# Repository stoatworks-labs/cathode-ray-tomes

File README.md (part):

# Cathode Ray Tomes

> **AI-assisted project.** This codebase was created with [Claude](https://claude.com/claude-code)
> (Anthropic), directed and reviewed by a human author.
> I've run the corpus index, the ingestion pipeline and the web application end to end against
> the real ArcadeRTFM corpus. The Pong KiCad conversion has a verified component complement and
> BOM, but only eight of its signal nets (the video output chain) have been traced. The Battlezone
> Math Box and Tempest auxiliary boards are traced in full, every net on their drawings, and each
> redrawn schematic is checked against its read by KiCad's own netlist. Nothing here has been
> checked against physical hardware.

Modern, searchable editions of service documentation: arcade boards, and the
consoles that came after them.

**It's here to help you fix boards.** The board conversions are
diagnostic aids. They answer "which chip is at C4, what does it do, and am I even
looking at the right revision", and they aren't trying to be complete clones.
A partial complement that gets you to the right chip is useful; a complete one
that's wrong about your board revision isn't. That's why Asteroids ships as
four separate boards rather than one averaged guess.

Arcade service manuals survive almost entirely as flat scans: page images with no text
layer, no structure and no way to search them. Cathode Ray Tomes rebuilds them as web
documents, with every page OCR'd and searchable, every machine cross-referenced against its
hardware specification and DIP switch settings, and (for a small number of boards) the
schematic rebuilt as a proper KiCad project with an accurate bill of materials.

Console service manuals are a different problem, and a much nicer one. Most of them
are native vector with a real text layer, so their schematic sheets already carry
designators, values and net names as text rather than as ink, which leaves nothing to OCR
and nothing to trace. Eleven consoles and handhelds are here, with 42 documents between
them; see `docs/EXTERNAL-SOURCES.md` for where they came from.

Not all of those are service manuals, and they don't pretend to be. Development
manuals and modchip installation guides have their own document types and sort after
every kind of service material, so a machine page shows the service manuals first.

## What the corpus actually is

I measured this rather than assuming it, from `https://arcadertfm.com/machines.json` and the
PDFs themselves:

| | |
|---|---|
| Machines (MAME-derived metadata) | 7,812 |
| Machines with documents | 1,384 |
| PDFs | 2,405 (~4.7 GB) |
| Schematic / drawing / wiring documents | 506 |
| PDFs containing a text layer | **0** |
| PDFs containing vector artwork | **0** |

Every page of every document is a single embedded raster image: bilevel CCITT/JBIG2 at
200–300 dpi for line drawings, JPEG/JPX greyscale for photographed pages. One file was
authored in Adobe Illustrator 9 and still contains only a placed scan. That one fact
drives the whole design: text has to be recovered by OCR, and diagrams have to be traced.

## Layout

```
src/            Cloudflare Worker (API + asset serving)
web/            Static front-end: browse, reader, schematic + BOM viewers
tools/          Ingestion, indexing, search and vectorisation pipeline
kicad/          KiCad conversions, one directory per board (jtcores' are GPL-3.0);
                kicad/chips/ holds jtcores' custom-chip redraws, also GPL-3.0
data/           Generated indexes (machines, docs, chips, postings)
cache/          Local ingest cache: PDFs, page images, OCR text (gitignored)
```

## Pipeline

```bash
python3 tools/build_index.py                    # normalise upstream metadata
python3 tools/ingest.py --workers 6             # fetch, rasterise, OCR, detect structure
python3 tools/backfill_structure.py [--force]   # add/refresh outlines on existing docs
python3 tools/detect_language.py                # which documents are not English
python3 tools/parts_rows.py --all               # re-read parts-list pages that lost their rows
python3 tools/build_search.py                   # sharded OCR postings + chip index
python3 tools/build_doc_stats.py                # fold page/section counts into the catalogue
python3 tools/build_drawings.py --images        # mark drawing pages; publish their scans
python3 tools/vectorise.py <docId> --pages 1,3  # trace line art to SVG
python3 tools/build_assets.py                   # assemble web/data/ for the deploy
python3 tools/check_pages.py                    # read what shipped; exit 1 on a bad page
```

`ingest.py` is resumable: finished documents are checkpointed in
`data/ingest-state.json` and skipped on a re-run.

## Notes on the hard parts

**The HTML manual is the main event, and the scan is the backup.** Each document is rebuilt
as a proper web page (headings, paragraphs, lists, callouts and tables), and that's what the
reader shows by default. The scan is kept as a "see original" reference for anything the OCR
couldn't carry.

That's what makes the whole thing cheap to serve. The full structured text and outline
for a 52-page manual is **24 KB gzipped**; the entire corpus of text is ~90 MB, which ships
as static assets beside the code. Page images, by comparison, would be 63,000 files and 8.9 GB.

**Two-column layout.** These manuals are set in two columns. Recognised lines have to be kept
in tesseract's own reading order, because sorting them top to bottom interleaves the columns
and turns the text into nonsense. This matters more than anything else for whether the output
is readable.

**Document structure.** The scans carry no font information, so headings are recovered
from geometry: tesseract emits word boxes alongside the text in a single pass, lines are
reassembled, and a line counts as a heading when it's set noticeably larger than the
document's own body text *and* reads like a heading (short, capitalised, often numbered
`A.` / `1.`). Contents pages and illustrated-parts-list pages are left out, because both set
their rows in large type and would otherwise flood the outline with entries pointing at
the sections they only reference. Headings wrapped across two lines are joined back up.

On the Asteroids TM-143 technical manual this recovers the actual structure (*Location
Setup → A. New Parts → B. Game Inspection → C. Game Installation → D. Self-Test Procedure
→ E. Game Play → Maintenance and Repair → A. Cleaning → B. Fuse Replacement → …*) from a
52-page scan with no text layer. That outline becomes the in-page navigation.

**Search.** Postings are built from the OCR text and sharded by leading character, so a
query only fetches the shards its terms touch and no single shard gets near the 25 MiB
limit on one static asset. Documents have to contain every term and are ranked by total
occurrences, so the manual that actually documents a part outranks a schematic that prints
it once in a corner. Searching `7400` finds the Pong schematic alongside every other board using that
chip, which is what a repair search actually looks like.

**OCR.** Quality follows the source scan. Dense schematic sheets return fragmentary text,
but helpfully still recover part numbers (`7400`, `74107`, `9316`), which is what a
repairer actually searches for. Typed manual pages come back clean.

**Tables and block order.** A page is stored as an ordered list of blocks, which is right
for prose and wrong for a ruled table: tesseract treats the vertical rule between two
columns as a block boundary, so flattening the page emits every item number, part number
and quantity first and every description afterwards. The parts extractor then pairs each
row's part number with the *next* row's item number, and 22% of recovered rows had no
usable description at all.

Nothing is lost, only unlabelled, because every cell still knows where it sat. `parts_rows.py`
re-reads those pages from their cached scans, bands the lines by vertical centre and
joins each row's cells back together, which is the shape the extractor already reads.
Both readings are then taken and the better one kept per page, scored on descriptions
recovered, so a page the banded read can't parse (Xevious prints no item-number
column, Tenpin prints its description first) keeps the flat one.

Its output lives in `cache/rows/`, which is **gitignored like the rest of the cache**.
Run it before `build_parts.py`, or the descriptions it recovered silently go back to
em-dashes on the next rebuild. It's incremental: 346 pages, six minutes cold, and
nothing on a re-run.

**A DIP-switch table arrived as a sentence, and nothing was feeding the machinery that
would have fixed it.** `build_blocks` has emitted a `tr` for any line carrying two or
more wide gaps since tables were added, and the reader splits a `tr` on those gaps into
cells. Nothing ever reached it: `ocr_page` built each line's text by joining tesseract's
words with single spaces, so the gaps that say where one cell ends and the next begins
didn't survive the read. 4-Player Football's option-switch page reached the reader as
`Off 70 seconds per coin F On 90 seconds per coin $ N` (two rows of a table set as one
paragraph), and every DIP-switch, option-switch and pin-out table in the corpus was in
the same state. Those are the pages a repairer actually opens.

The distances aren't subtle: on that page a word space is 8 pixels and the column gaps
are 43 to 251. What makes them unsafe on their own is that a gap wide enough to be a
column is also wide enough to be the hole OCR leaves where it dropped a word. So the
gaps are only a suggestion, and a cell start has to **repeat** down the page before a
split is kept. The Result column there begins at x = 459–462 on all nine of its rows,
while debris lands wherever it lands and gets dropped.

That repeat test is also the guard against the thing that must never happen. A page has to
show **three** columns before anything is split, because two is what two-column prose
looks like when tesseract reads across the gutter: those lines carry a single wide gap,
make two cells, and are left alone. On Hard Drivin' page 3-25 the flowchart boxes became
rows and the two columns of numbered prose beneath them didn't.

`page_tables.py` applies this to the corpus the way `parts_rows.py` applies its banding,
and for the same reason: `cache/text/` stores blocks, and the word boxes that say where
a cell began aren't in them, so the pages are read again from their cached scans. A page
is only kept if it gained a table **and** still says, word for word, what it said before,
which is what makes a 4,000-document backfill safe. A page whose re-read doesn't reproduce
its own published text didn't read the same way twice, and is left alone. The one
difference allowed is a word hyphenated across a line break, `Designator` becoming
`Desig-` / `nator` where the row broke out of its paragraph.

Its output is `data/tables/`, which unlike `cache/rows/` is **committed**, because
`web/data/doc/` is built from `cache/text/` plus the side-cars, and a gitignored one
reverts on the next rebuild with nothing to say it happened. It's merged in by
`build_assets.py --tables-only`, which leaves the corpus index alone for the same reason
`--boards-only` does. 12,145 pages across 1,810 documents are now set as tables, 244,719
rows, and `check_pages.py` reports the same as it did before.

**Not everything is in English.** 43 of these manuals are Japanese, and tesseract
run with `-l eng` doesn't so much fail on one as make things up: Super Puzzle Fighter's first
page came back as `yo09964Zd WO Ddivfay SARL 21 BHMGMII`, and with `-l jpn+eng` it's
`© CAPCOM CO., LTD. 1996 ALL RIGHTS RESERVED. 取扱説明書`. `detect_language.py` finds them
from the share of a document's prose that's English function words, then confirms by
re-reading one page in Japanese and counting the CJK. That's what tells a Japanese
manual from a parts catalogue, which is also short of function words but has no CJK at
all. The answer lives in `data/languages.json`, so the language is a property of the
document rather than a flag to remember.

Two things had to follow from that. `build_drawings.py` is calibrated on English OCR debris
and counts every kanji as a symbol, so a correctly read Japanese page scored 0.24-0.53
against a drawing threshold of 0.030 and would have been hidden for being legible.
And Japanese is written without spaces, so `build_search.py` indexes it as character
bigrams and the Worker splits a query the same way: 2,538 more terms for 0.8% more
index, with no dictionary and no segmenter.

**Checking what shipped.** Every check in the pipeline asks whether a document
*ingested*. `tools/check_pages.py` asks the next question: given what's in
`web/data/`, is there a page a reader would open and find unusable? It reads each page
the way the reader renders it and reports drawing debris set as prose, text the
extractor couldn't decode, a scan promised by `dw`/`dh` with no file behind it, a scan
published that no page points at, and a table row that can't be split into cells. It
exits non-zero when anything fires, so it belongs before a deploy rather than after one.

It exists because the alternative didn't work. The SCPH-70000's parts list shipped as
five thousand words of `U U U U U … C1692 C1693` for as long as the document was on the
site. The ingest had measured the problem, written it into the document's own metadata
and printed a warning, and the warning scrolled past in a build that prints a hundred
lines. It currently reports two one-cell table rows, which clear when those two
documents are next ingested.

**Drawing pages.** A page that's a drawing has no prose to rebuild, but OCR doesn't
return nothing for one. It returns the marks it found and calls them words. Rendered
as paragraphs, that reads as fluent nonsense, which was the worst thing on the site.
Those pages are now shown as the scan, with what OCR recovered kept underneath and
collapsed, because that's what the search index matched on.

Deciding which pages those are is the whole difficulty, and not because the nonsense
is hard to spot. Illustrated parts lists and DIP-switch tables score almost the same
as a schematic on any measure of how word-like the text is (they're part numbers and
abbreviations), and they're the most useful pages in the manual. So no page is hidden
on a score alone: the document's own outline heading, or the catalogue's record that the
document is a schematic package, has to agree with it. Pages where only the score
fires keep their text and are just marked as having come off a drawing.

**Vectorisation.** `tools/vectorise.py` traces bilevel line art to SVG. It recovers
**geometry, not meaning**: it doesn't recognise a resistor and redraw it as an IEC
symbol. Turning a traced diagram into standard schematic symbols is recognition work,
done by hand per diagram.

Measured properly, tracing *isn't* a size win. Per page of the Asteroids manual:
whole-page trace 109–267 KB gzipped, figure-only trace ~63 KB, the 150 dpi WebP 68–174 KB.
Traced scans are path-heavy because every stroke edge carries scan noise; despeckling and
tracing at 200 dpi roughly halves it, but raster still wins on bytes. What vector buys you
is resolution independence and theme-awareness, not smaller files. (The one exception is a
dense, line-dominated schematic sheet, where the earlier Pong measurement favoured SVG,
and that result doesn't generalise.)

**KiCad conversion.** There's no tool that turns a 1974 Atari drawing into a netlist, so
each board is built by hand. Each conversion says on the site whether its nets have been
traced or only the component complement captured.

The Battlezone Math Box (Auxiliary PCB 035678-01) is the first with everything: I read all
186 nets off DP-156 sheet 3 Side B into `boards/battlezone-math-box.nets`, and from there it's
scripted. `tools/build_board_nets.py` argues with the read (pins that don't exist, outputs
fighting, pins nobody mentioned, signatures that disagree), the KiCad schematic is drawn from
it across eight sheets, `tools/check_board_schematic.py` proves KiCad's netlist says the same
thing, and the board view gets the nets on its IC pads. The board page links the redrawn sheets
beside the scan. The scan still wins an argument.

The Tempest Auxiliary PCB (037585-01) is the second, and the bigger: the same Math Box at
different positions, plus the high-score EAROM and the charge pump that makes its -28V, both
POKEYs and the audio stage, 216 nets in all. Its Math Box agrees with Battlezone's net for net,
which is about the best check two drawings can give each other. Where the sheet contradicts
itself, the board page says so instead of picking quietly.

Forty-three more boards come from [jtcores](https://github.com/jotego/jtcores), jotego's FPGA
recreations of arcade hardware, whose contributors redraw each board they study in KiCad:
Gradius III, the CP System III, Sega System 18, Twin 16, Sunset Riders and the rest. Those
drawings are theirs and GPL-3.0. `kicad/<slug>/` holds each one unchanged, with its licence
and a notice saying who drew it and what was added here, and everything made from it — the
board view, the netlist, the chip lookup and the bill of materials — is under the same
licence. The board page says whose drawing it is.

Every board with a KiCad schematic can be opened in the page itself, through
[KiCanvas](https://kicanvas.org): pan, zoom, step between sheets, click a chip or a net. The
sheets come straight from this repository on GitHub, so nothing extra ships with the site.

jtcores also redraws thirteen custom chips from the inside: nine Konami gate arrays from the
Twin 16 boards, three Capcom DL-series chips from Pang, and Konami's 052535 video DAC, most of
them cell by cell off a photograph of the die. A dead custom is a common fault and the part
cannot be bought, so each has a page of its own (`/chip/<part>`): what it does, every pin and
which way it points, the boards and machines here that carry it, and the drawing itself. They
are in `kicad/chips/<slug>/`, unchanged and GPL-3.0 like the boards.

Sixteen of the CPU-less games of the Pong era — Pong itself, Breakout, Space Race, Stunt Cycle,
Jet Fighter, Rebound and the rest — get their connectivity from [DICE](https://github.com/mittonk/dice-libretro),
the emulator that runs them by simulating every chip. Its netlists are GPL-3.0 as well. They are
an emulator's model of the board rather than a drawing of it, so the conversion undoes DICE's
shortcuts (an RC delay standing in a wire is a wire again), leaves its analogue models off the
board, and compares it against the hand-read map where there is one.

## Deployment

The Worker and static assets build from GitHub via Cloudflare Workers Builds on push to
`main`. The corpus ships with them: `tools/build_assets.py` assembles the indexes and documents
in `web/data/`, the page scans the reader shows sit in `web/pages/`, and both are committed, so
a deploy publishes code and corpus together. Original PDFs aren't hosted; `/pdf/<id>`
redirects to the source archive. CI never touches `cache/`.

```bash
npm ci                 # install pinned wrangler
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
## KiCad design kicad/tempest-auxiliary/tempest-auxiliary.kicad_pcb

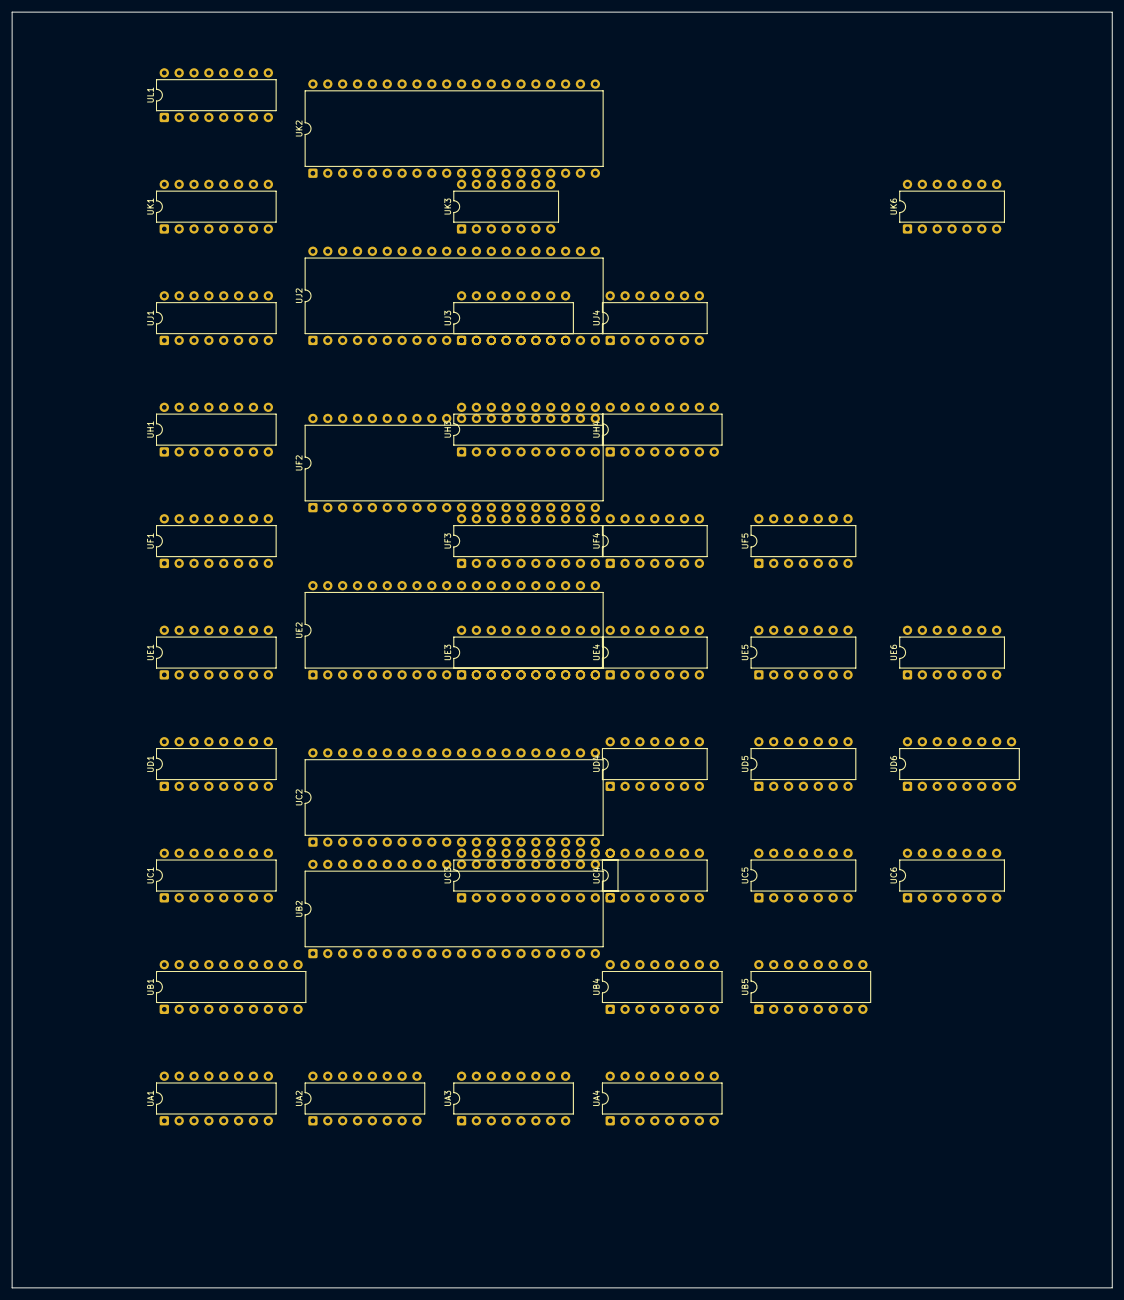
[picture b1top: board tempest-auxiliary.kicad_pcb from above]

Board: 2 copper layers, 188.0 x 218.0 mm, 41 parts (0 on the bottom side), 159 nets, no tracks yet.

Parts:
UA1: 82S123; DIP-16_W7.62mm
UA2: 74109; DIP-16_W7.62mm
UA3: 74LS174; DIP-16_W7.62mm
UA4: 74LS191; DIP-16_W7.62mm
UB1: 74LS374; DIP-20_W7.62mm
UB2: C012294-01; DIP-40_W15.24mm
UB4, UB5: 74LS139; DIP-16_W7.62mm
UC1: 74LS161; DIP-16_W7.62mm
UC2: C012294-01; DIP-40_W15.24mm
UC3: ER2055; DIP-22_W7.62mm
UC4: 74LS32; DIP-14_W7.62mm
UC5: 74LS10; DIP-14_W7.62mm
UC6: 74LS74; DIP-14_W7.62mm
UD1: 74LS161; DIP-16_W7.62mm
UD4: 74LS00; DIP-14_W7.62mm
UD5: 74LS74; DIP-14_W7.62mm
UD6: 74LS157; DIP-16_W7.62mm
UE1: 82S129; DIP-16_W7.62mm
UE2: 137004-001; DIP-40_W15.24mm
UE3: 74LS244; DIP-20_W7.62mm
UE4: 74S08; DIP-14_W7.62mm
UE5: 74S86; DIP-14_W7.62mm
UE6: 4584B; DIP-14_W7.62mm
UF1: 82S129; DIP-16_W7.62mm
UF2: 137004-001; DIP-40_W15.24mm
UF3: 74LS374; DIP-20_W7.62mm
UF4: 74LS14; DIP-14_W7.62mm
UF5: 74S03; DIP-14_W7.62mm
UH1: 82S129; DIP-16_W7.62mm
UH3: 74LS244; DIP-20_W7.62mm
UH4: 74LS174; DIP-16_W7.62mm
UJ1: 82S129; DIP-16_W7.62mm
UJ2: 137004-001; DIP-40_W15.24mm
UJ3: 74LS175; DIP-16_W7.62mm
UJ4: 74LS02; DIP-14_W7.62mm
UK1: 82S129; DIP-16_W7.62mm
UK2: 137004-001; DIP-40_W15.24mm
UK3, UK6: LM324; DIP-14_W7.62mm
UL1: 82S129; DIP-16_W7.62mm

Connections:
+5V: UA1.16, UA2.16, UA3.16, UA4.16, UB1.20, UB2.17, UB4.16, UB5.16, UC1.16, UC2.17, UC3.6, UC4.14, UC5.14, UC6.14, UD1.16, UD4.14, UD5.14, UD6.16, UE1.16, UE2.10, UE3.20, UE4.14, UE5.14, UE6.14, UF1.16, UF2.10, UF3.20, UF4.14, UF5.14, UH1.16, UH3.20, UH4.16, UJ1.16, UJ2.10, UJ3.16, UJ4.14, UK1.16, UK2.10, UK6.5, UL1.16
/BEGIN: UA1.15, UA2.3, UA2.7, UD5.13, UE4.12
/CLK: UD5.11, UE4.4, UF4.2
/EARCON: UB4.11, UJ3.9
/EARD: UB5.11, UE3.1, UF4.9
/EARWR: UA3.9, UB4.12, UF3.11
/I/O: UB4.1, UC4.1
/OL: UC4.11, UH4.9
/PCEN: UC1.9, UC1.10, UD1.9, UD1.10, UE4.11
/POKEY1: UB2.30, UB5.4
/POKEY2: UB5.5, UC2.30
/RESET: UH4.1, UJ3.1
/STREN: UB5.12, UF4.13
/WRITE: UC4.2, UC4.13, UC5.8
/YHI: UB5.9, UE2.40, UJ2.40
/YLO: UB5.10, UF2.40, UK2.40
A0: UB1.8, UE2.1, UF2.1, UJ2.1, UK2.1, UL1.9
A1: UB1.13, UE2.2, UF2.2, UJ2.2, UK2.2, UL1.10
A1-1: UA1.1, UB1.19, UD1.3
A1-2: UA1.2, UB1.2, UD1.4
A1-3: UA1.3, UB1.16, UD1.5
A1-4: UA1.4, UB1.5, UD1.6
A1-5: UA1.5, UB1.15, UC1.3
A1-6: UA1.6, UB1.6, UC1.4
A1-7: UA1.7, UB1.12, UC1.5
A1-9: UA1.9, UB1.9, UC1.6
A2: UB1.7, UE2.3, UF2.3, UJ2.3, UK2.3, UL1.11
A3: UB1.14, UE2.4, UF2.4, UJ2.4, UK2.4, UL1.12
A3-2: UA3.2, UC3.8
A3-5: UA3.5, UC3.10
A3-7: UA3.7, UC3.12
A3-10: UA3.10, UC3.11
A3-12: UA3.12, UC3.9
A3-15: UA3.15, UC3.7
A4: UB1.4, UE2.20, UF2.20, UJ2.20, UK1.9, UK2.20
A5: UB1.17, UE2.19, UF2.19, UJ2.19, UK1.10, UK2.19
A6: UB1.3, UE2.18, UF2.18, UJ2.18, UK1.11, UK2.18
A7: UB1.18, UE2.17, UF2.17, UJ2.17, UK1.12, UK2.17
A8: UE2.14, UJ1.9, UJ2.14
A9: UF2.14, UJ1.10, UK2.14
A10: UE5.9, UJ1.11
A10*: UE2.13, UE5.8, UF2.13, UJ2.13, UK2.13
A11: UE2.12, UF2.12, UJ1.12, UJ2.12, UK2.12
A12: UD5.12, UH1.9
A13: UE2.27, UF2.27, UH1.10, UJ2.27, UK2.27
A14: UE2.28, UF2.28, UH1.11, UJ2.28, UK2.28
A15: UE2.26, UF2.26, UH1.12, UJ2.26, UK2.26
A17: UE2.6, UF1.10, UF2.6, UJ2.6, UK2.6
A18: UD4.4, UD4.5, UE2.7, UF1.11, UF2.7, UF5.12, UF5.13, UJ2.7, UK2.7
A19: UE2.5, UF1.12, UF2.5, UJ2.5, UK2.5
B2-28: UB2.24, UB2.28
B4-5: UB4.5, UC4.10
B4-6: UB4.6, UC4.5
B4-7: UB4.7, UB5.1
B5-6: UB5.6, UC4.12
BEGIN: UA2.6, UB1.1, UD4.2
C: UE1.12, UK2.29
C2-28: UC2.24, UC2.28
C3-1: UC3.1, UE3.2, UF3.2
C3-2: UC3.2, UE3.4, UF3.5
C3-3: UC3.3, UE3.6, UF3.6
C3-4: UC3.4, UE3.8, UF3.9
C3-5: UC3.5, UE3.11, UF3.12
C3-20: UC3.20, UE3.13, UF3.15
C3-21: UC3.21, UE3.15, UF3.16
C3-22: UC3.22, UE3.17, UF3.19
C4-3: UB4.15, UC4.3
C4-6: UC4.6, UF4.5, UJ4.5
C4-8: UB5.15, UC4.8
C6-5: UA4.5, UC6.5
C11-2: UK3.2, UK3.6, UK3.9, UK3.13
CLK: UC1.2, UD1.2, UD4.1, UD5.3, UE2.15, UF2.15, UF4.1, UJ2.15, UJ4.1, UK2.15
D1-15: UC1.7, UD1.15
D4-6: UD4.6, UF5.5
D4-8: UD4.8, UD4.13, UF5.4
D4-11: UD4.11, UE4.13
D5-6: UD5.6, UE4.10
D6-4: UC6.2, UD6.4
D6-7: UC2.10, UD6.7
D6-9: UC2.13, UD6.9
D6-12: UA4.14, UC6.3, UD6.12
E2-9: UE2.9, UJ2.8
E2-21: UE2.21, UJ2.16
E3MHZ: UA2.2, UC5.5, UC5.9, UH3.7, UJ4.2
E4-6: UB1.11, UE4.6
E4-8: UE4.8, UE5.10
E5-11: UD4.10, UE5.11
E6-6: UD6.14, UE6.6
E6-8: UD6.13, UE6.8
E6-10: UD6.3, UE6.10
E6-12: UD6.2, UE6.12
EAB0: UA1.10, UA3.6, UB2.36, UC2.36
EAB1: UA1.11, UA3.11, UB2.35, UC2.35
EAB2: UA1.12, UA3.4, UB2.34, UC2.34
EAB3: UA1.13, UA3.13, UB2.33, UC2.33
EAB4: UA1.14, UA3.3, UB5.2, UB5.14
EAB5: UA3.14, UB5.3, UB5.13
EAB6: UB4.2, UB4.14
EAB7: UB4.3, UB4.13
EDB0: UB2.38, UC2.38, UE3.7, UH3.6, UH4.14, UJ2.25, UJ2.36, UK2.25, UK2.36
EDB1: UB2.39, UC2.39, UE3.5, UH3.4, UH4.13, UJ2.24, UJ2.37, UK2.24, UK2.37
EDB2: UB2.40, UC2.40, UE3.3, UH3.2, UH4.11, UJ2.23, UJ2.38, UK2.23, UK2.38
EDB3: UB2.2, UC2.2, UE3.18, UH3.17, UH4.6, UJ2.22, UJ2.39, UK2.22, UK2.39
EDB4: UB2.3, UC2.3, UE2.25, UE2.36, UE3.9, UF2.25, UF2.36, UH3.8
EDB5: UB2.4, UC2.4, UE2.24, UE2.37, UE3.12, UF2.24, UF2.37, UH3.11
EDB6: UB2.5, UC2.5, UE2.23, UE2.38, UE3.14, UF2.23, UF2.38, UF3.7
EDB7: UB2.6, UC2.6, UE2.22, UE2.39, UE3.16, UF2.22, UF2.39, UF5.8, UH3.15
EPHI2: UB2.7, UC2.7, UC5.4, UC5.11, UJ4.6
ER/WB: UB2.32, UC2.32, UC4.4, UF4.11
F2-8: UF2.8, UJ2.9
F2-9: UF2.9, UK2.8
F2-16: UF2.16, UJ2.21
F2-21: UF2.21, UK2.16
F2-33: UF2.33, UJ2.29
F4-6: UC5.3, UF4.6
F4-12: UF4.12, UF5.9
FLIP: UD6.1, UH4.10
GND: UA1.8, UA2.8, UA3.8, UA4.1, UA4.4, UA4.8, UA4.9, UA4.10, UA4.15, UB1.10, UB2.1, UB4.8, UB5.8, UC1.8, UC2.1, UC3.18, UC3.19, UC4.7, UC5.7, UC6.7, UD1.8, UD4.7, UD5.7, UD6.8, UD6.15, UE1.8, UE1.13, UE1.14, UE2.30, UE3.10, UE4.7, UE5.7, UE6.7, UF1.8, UF1.13, UF1.14, UF2.30, UF3.10, UF4.7, UF5.7, UH1.8, UH1.13, UH1.14, UH3.1, UH3.10, UH4.8, UJ1.8, UJ1.13, UJ1.14, UJ2.30, UJ3.8, UJ4.7, UK1.8, UK1.13, UK1.14, UK2.30, UK3.4, UK6.11, UL1.8, UL1.13, UL1.14
H3-3: UF3.3, UH3.3, UJ3.4
H3-5: UF3.4, UH3.5
H3-9: UF3.8, UH3.9
H3-12: UF3.13, UH3.12
H3-14: UF3.14, UH3.14, UJ3.5
H3-16: UF3.17, UH3.16, UJ3.13
H3-18: UF3.18, UH3.18, UJ3.12
J: UD4.12, UE1.10
J2-33: UE2.29, UJ2.33
J3-2: UC3.17, UJ3.2
J3-7: UC3.13, UJ3.7
J3-11: UC3.15, UF3.1, UJ3.11
J3-15: UC3.16, UJ3.15
K2-33: UF2.29, UK2.33
K3-1: UK3.1, UK3.7, UK3.8, UK3.14
LDAB: UE4.5, UF1.9
M: UE1.11, UE4.9
M START: UA2.1, UJ4.4
MA0: UD1.14, UE1.5, UF1.5, UH1.5, UJ1.5, UK1.5, UL1.5
MA1: UD1.13, UE1.6, UF1.6, UH1.6, UJ1.6, UK1.6, UL1.6
MA2: UD1.12, UE1.7, UF1.7, UH1.7, UJ1.7, UK1.7, UL1.7
MA3: UD1.11, UE1.4, UF1.4, UH1.4, UJ1.4, UK1.4, UL1.4
MA4: UC1.14, UE1.3, UF1.3, UH1.3, UJ1.3, UK1.3, UL1.3
MA5: UC1.13, UE1.2, UF1.2, UH1.2, UJ1.2, UK1.2, UL1.2
MA6: UC1.12, UE1.1, UF1.1, UH1.1, UJ1.1, UK1.1, UL1.1
Q0: UD5.2, UF5.11, UK2.21
R0: UE2.16, UK2.9
R1-1: UA2.5, UA3.1, UB2.31, UC1.1, UC2.31, UD1.1, UD1.7
R15: UE2.8, UF5.6
R28-1: UK3.3, UK3.5, UK3.10, UK3.12
R54-1: UA4.11, UC6.1, UC6.4, UD5.1, UD5.4, UD5.10
R/WB: UC4.9, UC5.10, UF4.10
S: UD4.9, UE1.9
S0: UE2.34, UE5.13
S1: UE2.31, UE5.12
SAEN1: UC1.11, UE1.15, UF1.15, UH1.15, UJ1.15, UK1.15, UL1.15
STOP: UD5.9, UF5.10, UJ4.3
TBC0: UA4.3, UB2.14
TBC1: UA4.2, UB2.15
TBC2: UA4.6, UB2.12
TBC3: UA4.7, UB2.13

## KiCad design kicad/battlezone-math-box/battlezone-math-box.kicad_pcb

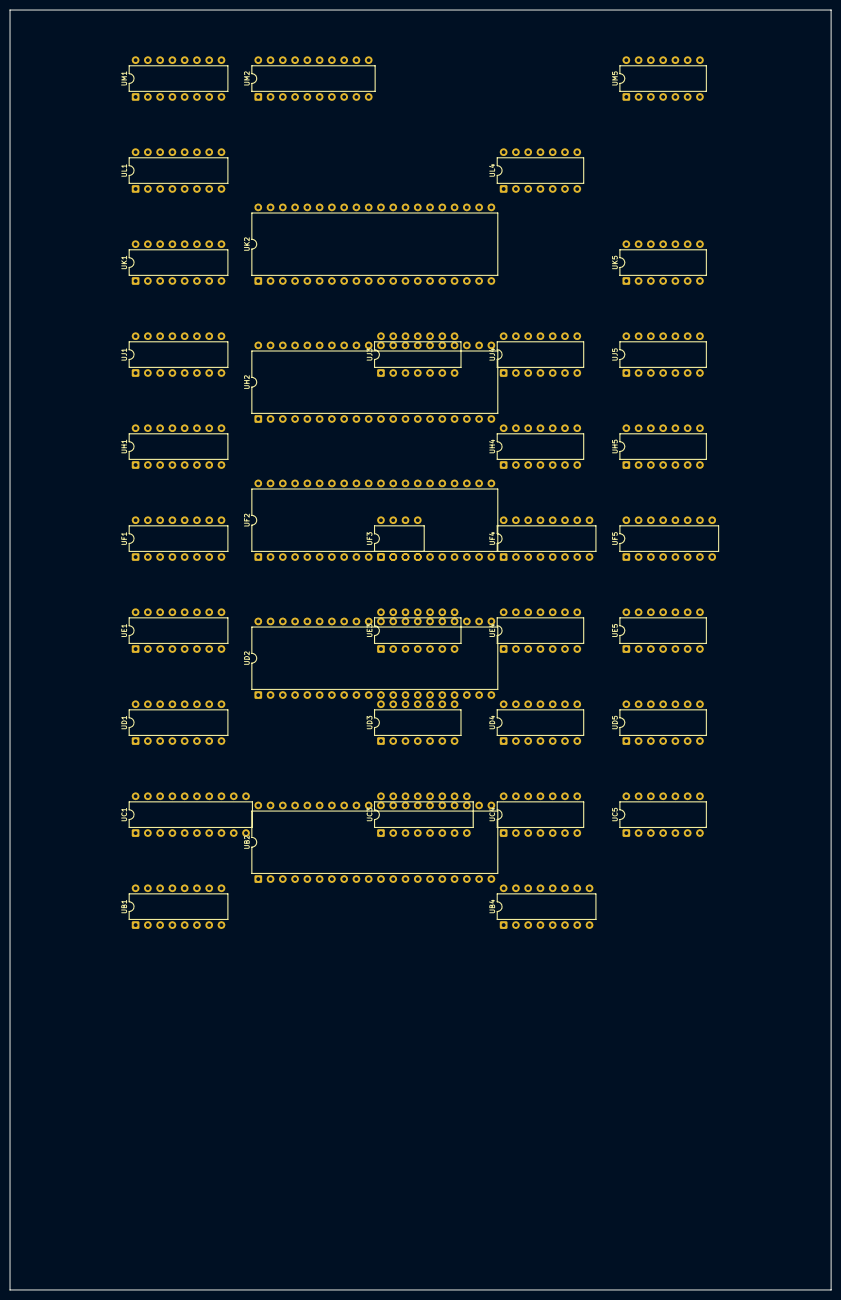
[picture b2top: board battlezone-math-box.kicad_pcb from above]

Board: 2 copper layers, 170.0 x 265.0 mm, 37 parts (0 on the bottom side), 138 nets, no tracks yet.

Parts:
UB1: 82S123; DIP-16_W7.62mm
UB2: C012294-01; DIP-40_W15.24mm
UB4: 74109; DIP-16_W7.62mm
UC1: 74LS374; DIP-20_W7.62mm
UC3: 74LS139; DIP-16_W7.62mm
UC4: 74LS32; DIP-14_W7.62mm
UC5: 74LS74; DIP-14_W7.62mm
UD1: 74LS161; DIP-16_W7.62mm
UD2: 137004-001; DIP-40_W15.24mm
UD3: 74LS00; DIP-14_W7.62mm
UD4: 74LS02; DIP-14_W7.62mm
UD5: 74S08; DIP-14_W7.62mm
UE1: 74LS161; DIP-16_W7.62mm
UE3: 74S03; DIP-14_W7.62mm
UE4: 74LS04; DIP-14_W7.62mm
UE5: 74S86; DIP-14_W7.62mm
UF1: 82S129; DIP-16_W7.62mm
UF2: 137004-001; DIP-40_W15.24mm
UF3: 555; DIP-8_W7.62mm
UF4, UF5: 74LS161; DIP-16_W7.62mm
UH1: 82S129; DIP-16_W7.62mm
UH2: 137004-001; DIP-40_W15.24mm
UH4, UH5: 74LS164; DIP-14_W7.62mm
UJ1: 82S129; DIP-16_W7.62mm
UJ3: CD4066; DIP-14_W7.62mm
UJ4: 74LS20; DIP-14_W7.62mm
UJ5: 74LS74; DIP-14_W7.62mm
UK1: 82S129; DIP-16_W7.62mm
UK2: 137004-001; DIP-40_W15.24mm
UK5: LM324; DIP-14_W7.62mm
UL1: 82S129; DIP-16_W7.62mm
UL4: CD4066; DIP-14_W7.62mm
UM1: 82S129; DIP-16_W7.62mm
UM2: 74LS273; DIP-20_W7.62mm
UM5: LM324; DIP-14_W7.62mm

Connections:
+5V: UB1.16, UB2.17, UB4.16, UC1.20, UC3.16, UC4.14, UC5.14, UD1.16, UD2.10, UD3.14, UD4.14, UD5.14, UE1.16, UE3.14, UE4.14, UE5.14, UF1.16, UF2.10, UF3.4, UF3.8, UF4.16, UF5.16, UH1.16, UH2.10, UH4.14, UH5.14, UJ1.16, UJ3.1, UJ3.11, UJ3.14, UJ4.14, UJ5.14, UK1.16, UK2.10, UL1.16, UL4.14, UM1.16, UM2.20, UM5.12
+22V: UK5.4, UM5.4
/BEGIN: UB1.15, UB4.3, UB4.7, UC5.13, UD5.13
/CLK: UC5.11, UD5.9, UE4.10
/OUTPUT LATCH: UC4.8, UM2.11
/SWITCHES: UB2.30, UC3.11
/YHI: UC3.7, UF2.40, UK2.40
/YLO: UC3.6, UD2.40, UH2.40
A0: UC1.8, UD2.1, UF2.1, UH2.1, UK2.1, UM1.9
A1: UC1.13, UD2.2, UF2.2, UH2.2, UK2.2, UM1.10
A2: UC1.7, UD2.3, UF2.3, UH2.3, UK2.3, UM1.11
A3: UC1.14, UD2.4, UF2.4, UH2.4, UK2.4, UM1.12
A4: UC1.4, UD2.20, UF2.20, UH2.20, UK2.20, UL1.9
A5: UC1.17, UD2.19, UF2.19, UH2.19, UK2.19, UL1.10
A6: UC1.3, UD2.18, UF2.18, UH2.18, UK2.18, UL1.11
A7: UC1.18, UD2.17, UF2.17, UH2.17, UK2.17, UL1.12
A8: UF2.14, UK1.9, UK2.14
A9: UD2.14, UH2.14, UK1.10
A10: UE5.10, UK1.11
A10*: UD2.13, UE5.8, UF2.13, UH2.13, UK2.13
A11: UD2.12, UF2.12, UH2.12, UK1.12, UK2.12
A12: UC5.12, UJ1.9
A13: UD2.27, UF2.27, UH2.27, UJ1.10, UK2.27
A14: UD2.28, UF2.28, UH2.28, UJ1.11, UK2.28
A15: UD2.26, UF2.26, UH2.26, UJ1.12, UK2.26
A16: UD5.10, UH1.9
A17: UD2.6, UF2.6, UH1.10, UH2.6, UK2.6
A18: UD2.7, UD3.4, UD3.5, UE3.9, UE3.10, UF2.7, UH1.11, UH2.7, UK2.7
A19: UD2.5, UF2.5, UH1.12, UH2.5, UK2.5
A20: UD3.12, UF1.9
A21: UD3.9, UF1.10
A22: UD5.4, UF1.11
A23: UD2.29, UF1.12
B1-1: UB1.1, UC1.19, UE1.3
B1-2: UB1.2, UC1.2, UE1.4
B1-3: UB1.3, UC1.16, UE1.5
B1-4: UB1.4, UC1.5, UE1.6
B1-5: UB1.5, UC1.15, UD1.3
B1-6: UB1.6, UC1.6, UD1.4
B1-7: UB1.7, UC1.12, UD1.5
B1-9: UB1.9, UC1.9, UD1.6
B2-28: UB2.24, UB2.28
B4-9: UB4.9, UB4.13, UB4.14, UH4.8, UH5.8
BEGIN: UB4.6, UC1.1, UD5.2
C3-4: UC3.4, UD4.11, UD4.12
C3-9: UC3.9, UC4.12
C3-10: UC3.10, UC4.9
C3-12: UC3.12, UC4.5
C4-6: UC3.1, UC4.6
C4-11: UC4.11, UD4.3, UE4.5
C5-6: UC5.6, UD5.5
C9-1: UJ3.8, UJ3.10
C11-1: UF3.2, UF3.6
C14-1: UJ3.2, UJ3.4
CLK: UC5.3, UD1.2, UD2.15, UD4.10, UD5.1, UE1.2, UE4.11, UF2.15, UH2.15, UK2.15
D2-8: UD2.8, UH2.9
D2-9: UD2.9, UK2.16
D2-16: UD2.16, UH2.21
D2-21: UC5.2, UD2.21, UE3.8
D2-33: UD2.33, UH2.29
D3-3: UC4.10, UD3.3
D3-6: UD3.6, UE3.12
D3-8: UD3.8, UD5.12
D3-11: UD3.10, UD3.11, UE3.13
D4-4: UD3.2, UD4.4
D4-13: UD4.13, UE3.1
D5-6: UD5.6, UE5.9
D5-8: UC1.11, UD5.8
D5-11: UD1.9, UD1.10, UD5.11, UE1.9, UE1.10
E1-15: UD1.7, UE1.15
E3-11: UE3.11, UK2.8
E3MHZ: UB4.2, UD3.1, UD4.8, UJ4.2
E4-2: UE4.2, UF4.9
E4-4: UE4.4, UF5.9
E4-6: UE4.6, UJ4.4, UJ4.5
E4-8: UC4.4, UE4.8
E4-12: UD4.5, UE4.12
E5-3: UE5.3, UH5.1, UH5.2
E5-6: UE5.2, UE5.6
E5-11: UD3.13, UE5.11
EAB0: UB1.10, UB2.36
EAB1: UB1.11, UB2.35
EAB2: UB1.12, UB2.34
EAB3: UB1.13, UB2.33, UC3.2
EAB4: UB1.14, UC3.3
EDB0: UB2.38, UD2.25, UD2.36, UF2.25, UF2.36, UM2.14
EDB1: UB2.39, UD2.24, UD2.37, UF2.24, UF2.37, UM2.7
EDB2: UB2.40, UD2.23, UD2.38, UF2.23, UF2.38, UM2.13
EDB3: UB2.2, UD2.22, UD2.39, UF2.22, UF2.39, UM2.8
EDB4: UB2.3, UH2.25, UH2.36, UK2.25, UK2.36, UM2.4
EDB5: UB2.4, UH2.24, UH2.37, UK2.24, UK2.37, UM2.17
EDB6: UB2.5, UH2.23, UH2.38, UK2.23, UK2.38, UM2.3
EDB7: UB2.6, UE3.3, UH2.22, UH2.39, UK2.22, UK2.39, UM2.18
ENGINE REV EN: UL4.13, UM2.5
EPHI2: UB2.7, UD4.2, UE4.13, UJ4.1
ER/WB: UB2.32, UC4.13, UD4.6, UE4.9
EXPLO L/S: UL4.5, UM2.6
F2-8: UF2.8, UK2.9
F2-9: UF2.9, UH2.8
F2-16: UF2.16, UK2.21
F2-21: UF2.21, UH2.16
F2-33: UF2.33, UK2.29
F3-3: UF3.3, UF4.2, UF5.2
F4-15: UE4.1, UF4.15
F5-15: UE4.3, UF5.15
GND: UB1.8, UB2.1, UB4.8, UC1.10, UC3.8, UC4.7, UC5.7, UD1.8, UD2.30, UD3.7, UD4.7, UD5.7, UE1.8, UE3.7, UE4.7, UE5.7, UF1.8, UF1.13, UF1.14, UF2.30, UF3.1, UF4.3, UF4.4, UF4.6, UF4.8, UF5.3, UF5.6, UF5.8, UH1.8, UH1.13, UH1.14, UH2.30, UH4.7, UH5.7, UJ1.8, UJ1.13, UJ1.14, UJ3.7, UJ4.7, UJ5.7, UK1.8, UK1.13, UK1.14, UK2.30, UK5.11, UL1.8, UL1.13, UL1.14, UL4.1, UL4.4, UL4.7, UL4.8, UM1.8, UM1.13, UM1.14, UM2.10, UM5.11
H2-33: UF2.29, UH2.33
H4-6: UH4.6, UJ4.9
H4-10: UH4.10, UJ4.10
H4-11: UH4.11, UJ4.12
H4-12: UE5.4, UH4.12, UJ4.13
H4-13: UH4.13, UJ5.11
H5-6: UE5.5, UH5.6
H5-13: UH4.1, UH4.2, UH5.13
J4-8: UJ4.8, UJ5.3
J5-6: UJ3.5, UJ5.2, UJ5.6
J5-8: UJ3.6, UJ5.8, UJ5.12
K2-31: UE5.12, UK2.31
K2-34: UE5.13, UK2.34
K5-7: UF3.5, UK5.6, UK5.7
M START: UB4.1, UD4.1
MA0: UE1.14, UF1.5, UH1.5, UJ1.5, UK1.5, UL1.5, UM1.5
MA1: UE1.13, UF1.6, UH1.6, UJ1.6, UK1.6, UL1.6, UM1.6
MA2: UE1.12, UF1.7, UH1.7, UJ1.7, UK1.7, UL1.7, UM1.7
MA3: UE1.11, UF1.4, UH1.4, UJ1.4, UK1.4, UL1.4, UM1.4
MA4: UD1.14, UF1.3, UH1.3, UJ1.3, UK1.3, UL1.3, UM1.3
MA5: UD1.13, UF1.2, UH1.2, UJ1.2, UK1.2, UL1.2, UM1.2
MA6: UD1.12, UF1.1, UH1.1, UJ1.1, UK1.1, UL1.1, UM1.1
MOTOR EN: UF4.1, UF5.1, UM2.19
R3-1: UB2.31, UD1.1, UE1.1, UE1.7
R22-1: UB4.5, UB4.11, UB4.15, UC5.1, UC5.4, UC5.10, UE5.1, UF4.5, UF4.7, UF4.10, UF5.4, UF5.5, UF5.7, UF5.10, UJ5.1, UJ5.4, UJ5.10, UJ5.13
R29-1: UK5.12, UL4.11
SAEN1: UD1.11, UF1.15, UH1.15, UJ1.15, UK1.15, UL1.15, UM1.15
SAEN2,3: UJ3.13, UM2.15
SHELL EN: UJ3.12, UM2.12
SHELL L/S: UL4.6, UM2.9
SOUND ENABLE: UH4.9, UH5.9, UL4.12, UM2.16
STOP: UC5.9, UD4.9, UE3.2

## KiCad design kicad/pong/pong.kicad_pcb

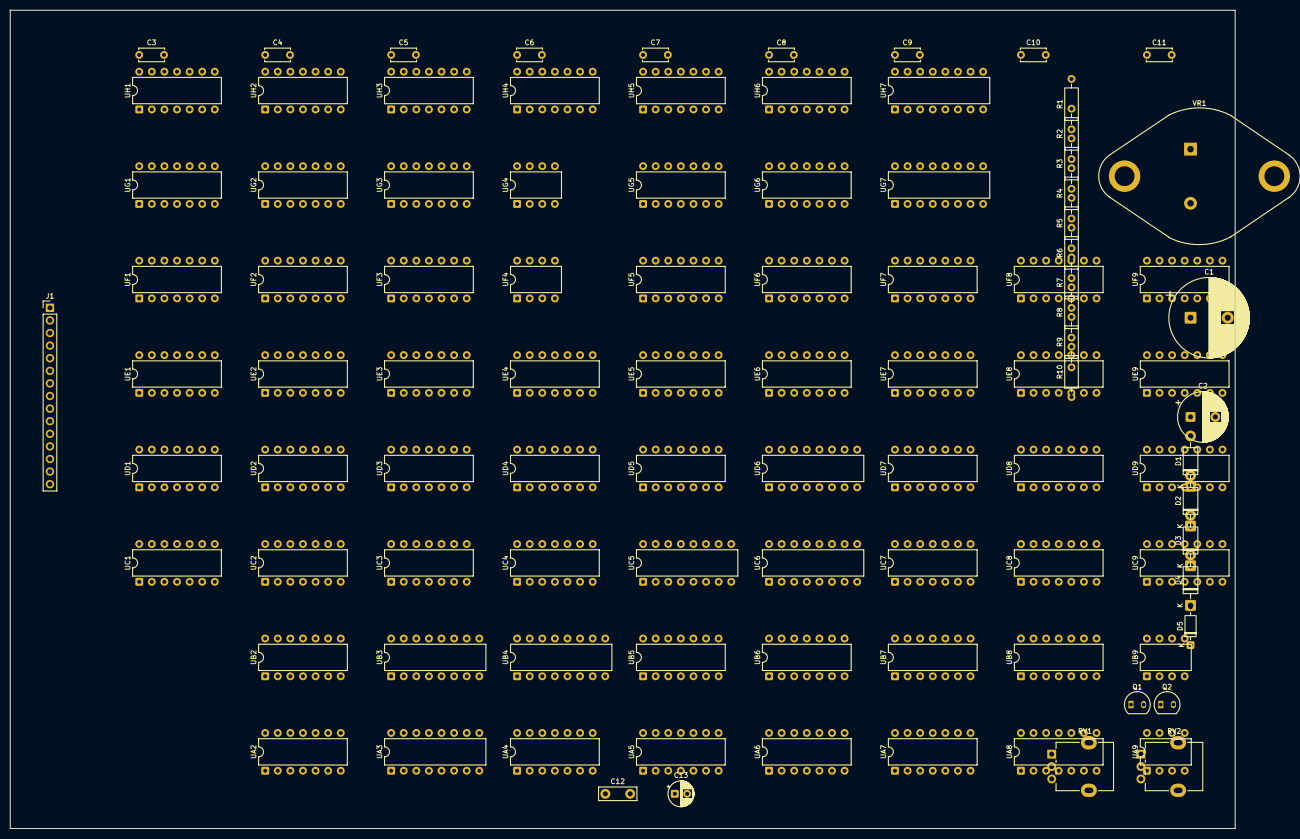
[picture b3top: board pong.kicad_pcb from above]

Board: 2 copper layers, 247.0 x 165.0 mm, 100 parts (0 on the bottom side), 5 nets, no tracks yet.

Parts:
C1: 8000uF; CP_Radial_D16.0mm_P7.50mm
C2: 470uF; CP_Radial_D10.0mm_P5.00mm
C3, C4, C5, C6, C7, C8, C9, C10, C11: 0.1uF; C_Disc_D5.0mm_W2.5mm_P5.00mm
C12: 1.0uF; C_Disc_D7.5mm_W2.5mm_P5.00mm
C13: 5.0uF; CP_Radial_D5.0mm_P2.50mm
D1, D2, D3, D4: 1N4001; D_DO-41_SOD81_P10.16mm_Horizontal
D5: 1N914; D_DO-35_SOD27_P7.62mm_Horizontal
J1: Edge Connector; PinHeader_1x15_P2.54mm_Vertical
Q1: 2N3643; TO-92-2
Q2: 2N3644; TO-92-2
R1: 2.2M; R_Axial_DIN0207_L6.3mm_D2.5mm_P10.16mm_Horizontal
R2: 330K; R_Axial_DIN0207_L6.3mm_D2.5mm_P10.16mm_Horizontal
R3: 2.2K; R_Axial_DIN0207_L6.3mm_D2.5mm_P10.16mm_Horizontal
R4: 1K; R_Axial_DIN0207_L6.3mm_D2.5mm_P10.16mm_Horizontal
R5: 1M; R_Axial_DIN0207_L6.3mm_D2.5mm_P10.16mm_Horizontal
R6, R7: 330R; R_Axial_DIN0207_L6.3mm_D2.5mm_P10.16mm_Horizontal
R8: 100R; R_Axial_DIN0207_L6.3mm_D2.5mm_P10.16mm_Horizontal
R9: 5.6K; R_Axial_DIN0207_L6.3mm_D2.5mm_P10.16mm_Horizontal
R10: 50K; R_Axial_DIN0207_L6.3mm_D2.5mm_P10.16mm_Horizontal
RV1: 50K POT (Player 1); Potentiometer_Alpha_RD901F-40-00D_Single_Vertical
RV2: 50K POT (Player 2); Potentiometer_Alpha_RD901F-40-00D_Single_Vertical
UA2: 74107; DIP-14_W7.62mm
UA3: 9316; DIP-16_W7.62mm
UA4: 7486; DIP-14_W7.62mm
UA5: 7474; DIP-14_W7.62mm
UA6: 7450; DIP-14_W7.62mm
UA7: 7420; DIP-14_W7.62mm
UA8: 7493; DIP-14_W7.62mm
UA9: 555; DIP-8_W7.62mm
UB2, UB7: 7400; DIP-14_W7.62mm
UB3: 9316; DIP-16_W7.62mm
UB4: 7483; DIP-16_W7.62mm
UB5: 7474; DIP-14_W7.62mm
UB6: 7450; DIP-14_W7.62mm
UB8: 7493; DIP-14_W7.62mm
UB9: 555; DIP-8_W7.62mm
UC1, UC3: 7400; DIP-14_W7.62mm
UC2: 7474; DIP-14_W7.62mm
UC4: 7410; DIP-14_W7.62mm
UC5: 7448; DIP-16_W7.62mm
UC6: 74153; DIP-16_W7.62mm
UC7: 7490; DIP-14_W7.62mm
UC8: 74107; DIP-14_W7.62mm
UC9: 7404; DIP-14_W7.62mm
UD1: 7404; DIP-14_W7.62mm
UD2: 7402; DIP-14_W7.62mm
UD3: 7430; DIP-14_W7.62mm
UD4, UD5, UD8: 7410; DIP-14_W7.62mm
UD6: 74153; DIP-16_W7.62mm
UD7: 7490; DIP-14_W7.62mm
UD9: 74107; DIP-14_W7.62mm
UE1, UE6: 7400; DIP-14_W7.62mm
UE2: 7410; DIP-14_W7.62mm
UE3, UE5: 7427; DIP-14_W7.62mm
UE4: 7404; DIP-14_W7.62mm
UE7: 7474; DIP-14_W7.62mm
UE8, UE9: 7493; DIP-14_W7.62mm
UF1: 7433; DIP-14_W7.62mm
UF2: 7425; DIP-14_W7.62mm
UF3, UF6: 74107; DIP-14_W7.62mm
UF4: 555; DIP-8_W7.62mm
UF5: 7402; DIP-14_W7.62mm
UF7: 7430; DIP-14_W7.62mm
UF8, UF9: 7493; DIP-14_W7.62mm
UG1: 7402; DIP-14_W7.62mm
UG2: 7427; DIP-14_W7.62mm
UG3: 7400; DIP-14_W7.62mm
UG4: 555; DIP-8_W7.62mm
UG5: 7410; DIP-14_W7.62mm
UG6: 74107; DIP-14_W7.62mm
UG7: 9316; DIP-16_W7.62mm
UH1, UH4, UH5: 7400; DIP-14_W7.62mm
UH2: 74107; DIP-14_W7.62mm
UH3: 7474; DIP-14_W7.62mm
UH6: 7420; DIP-14_W7.62mm
UH7: 9316; DIP-16_W7.62mm
VR1: LM309K; TO-3

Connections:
+5V: C3.1, C4.1, C5.1, C6.1, C7.1, C8.1, C9.1, C10.1, C11.1, UA2.14, UA3.16, UA4.14, UA5.14, UA6.14, UA7.14, UA8.5, UA9.8, UB2.14, UB3.16, UB4.5, UB5.14, UB6.14, UB7.14, UB8.5, UB9.8, UC1.14, UC2.14, UC3.14, UC4.14, UC5.16, UC6.16, UC7.5, UC8.14, UC9.14, UD1.14, UD2.14, UD3.14, UD4.14, UD5.14, UD6.16, UD7.5, UD8.14, UD9.14, UE1.14, UE2.14, UE3.14, UE4.14, UE5.14, UE6.14, UE7.14, UE8.5, UE9.5, UF1.14, UF2.14, UF3.14, UF4.8, UF5.14, UF6.14, UF7.14, UF8.5, UF9.5, UG1.14, UG2.14, UG3.14, UG4.8, UG5.14, UG6.14, UG7.16, UH1.14, UH2.14, UH3.14, UH4.14, UH5.14, UH6.14, UH7.16
GND: C3.2, C4.2, C5.2, C6.2, C7.2, C8.2, C9.2, C10.2, C11.2, UA2.7, UA3.8, UA4.7, UA5.7, UA6.7, UA7.7, UA8.10, UA9.1, UB2.7, UB3.8, UB4.12, UB5.7, UB6.7, UB7.7, UB8.10, UB9.1, UC1.7, UC2.7, UC3.7, UC4.7, UC5.8, UC6.8, UC7.10, UC8.7, UC9.7, UD1.7, UD2.7, UD3.7, UD4.7, UD5.7, UD6.8, UD7.10, UD8.7, UD9.7, UE1.7, UE2.7, UE3.7, UE4.7, UE5.7, UE6.7, UE7.7, UE8.10, UE9.10, UF1.7, UF2.7, UF3.7, UF4.1, UF5.7, UF6.7, UF7.7, UF8.10, UF9.10, UG1.7, UG2.7, UG3.7, UG4.1, UG5.7, UG6.7, UG7.8, UH1.7, UH2.7, UH3.7, UH4.7, UH5.7, UH6.7, UH7.8
HV_SUM: UF2.13, UG1.4
NET: UF2.10, UG2.6
VIDEO_SUM: UE4.13, UF2.8

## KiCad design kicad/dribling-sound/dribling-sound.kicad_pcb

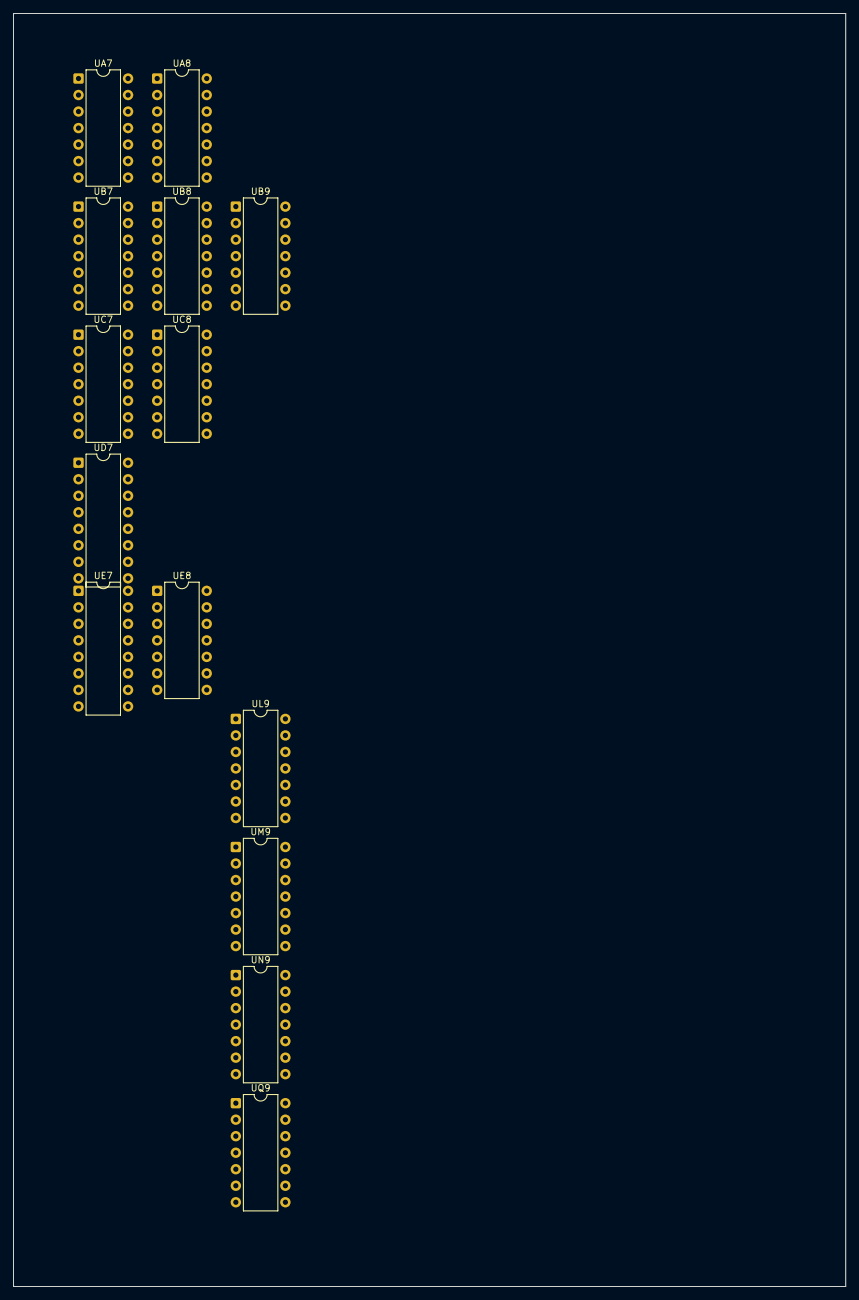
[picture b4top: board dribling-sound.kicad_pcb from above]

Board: 2 copper layers, 128.0 x 195.8 mm, 14 parts (0 on the bottom side), 23 nets, no tracks yet.

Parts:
UA7, UA8: 74LS164; DIP-14_W7.62mm
UB7: 7414; DIP-14_W7.62mm
UB8: 74LS86; DIP-14_W7.62mm
UB9: LM339; DIP-14_W7.62mm
UC7: 74LS107; DIP-14_W7.62mm
UC8: LM324; DIP-14_W7.62mm
UD7: 74LS161; DIP-16_W7.62mm
UE7: 74LS161; DIP-16_W7.62mm
UE8: 7408; DIP-14_W7.62mm
UL9: 7404; DIP-14_W7.62mm
UM9: 74393; DIP-14_W7.62mm
UN9: NE556; DIP-14_W7.62mm
UQ9: NE556; DIP-14_W7.62mm

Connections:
+5V: UA7.9, UA7.14, UA8.9, UA8.14, UB7.14, UB8.14, UB9.3, UC7.10, UC7.14, UD7.1, UD7.7, UD7.10, UD7.16, UE7.1, UE7.16, UE8.14, UL9.14, UM9.14, UN9.14, UQ9.4, UQ9.14
FISCHIO: UM9.2, UM9.12
FISCHIO.INV.INPUT: UL9.13, UM9.6, UM9.13
FISCHIO.INV.OUTPUT: UL9.12, UN9.4, UN9.10
FOLLA.C_IN: UA7.8, UA8.8, UB7.6
FOLLA.NOISE: UA7.13, UE8.2, UE8.9, UE8.13
GND: UA7.7, UA8.7, UB7.7, UB8.7, UB9.12, UC7.7, UC8.11, UD7.8, UE7.8, UE8.7, UL9.7, UM9.7, UN9.7, UQ9.7
INV1.INPUT: UB7.11, UC7.8, UC7.11, UE7.15
INV1.OUTPUT: UB7.10, UD7.9, UE7.9
INV2.INPUT: UB7.8, UB7.13, UC7.9
INV2.OUTPUT: UB7.12, UD7.2, UE7.2
unnamed: UN9.8, UN9.12
unnamed: UN9.1, UN9.2, UN9.6
unnamed: UQ9.1, UQ9.2
unnamed: UQ9.8, UQ9.12, UQ9.13
unnamed: UA7.1, UA7.2, UA8.13
unnamed: UA7.12, UB7.3
unnamed: UA8.1, UA8.2, UB8.3
unnamed: UA8.3, UB8.2
unnamed: UB7.4, UB8.1
unnamed: UD7.15, UE7.7, UE7.10
unnamed: UM9.1, UN9.5
unnamed: UQ9.5, UQ9.10

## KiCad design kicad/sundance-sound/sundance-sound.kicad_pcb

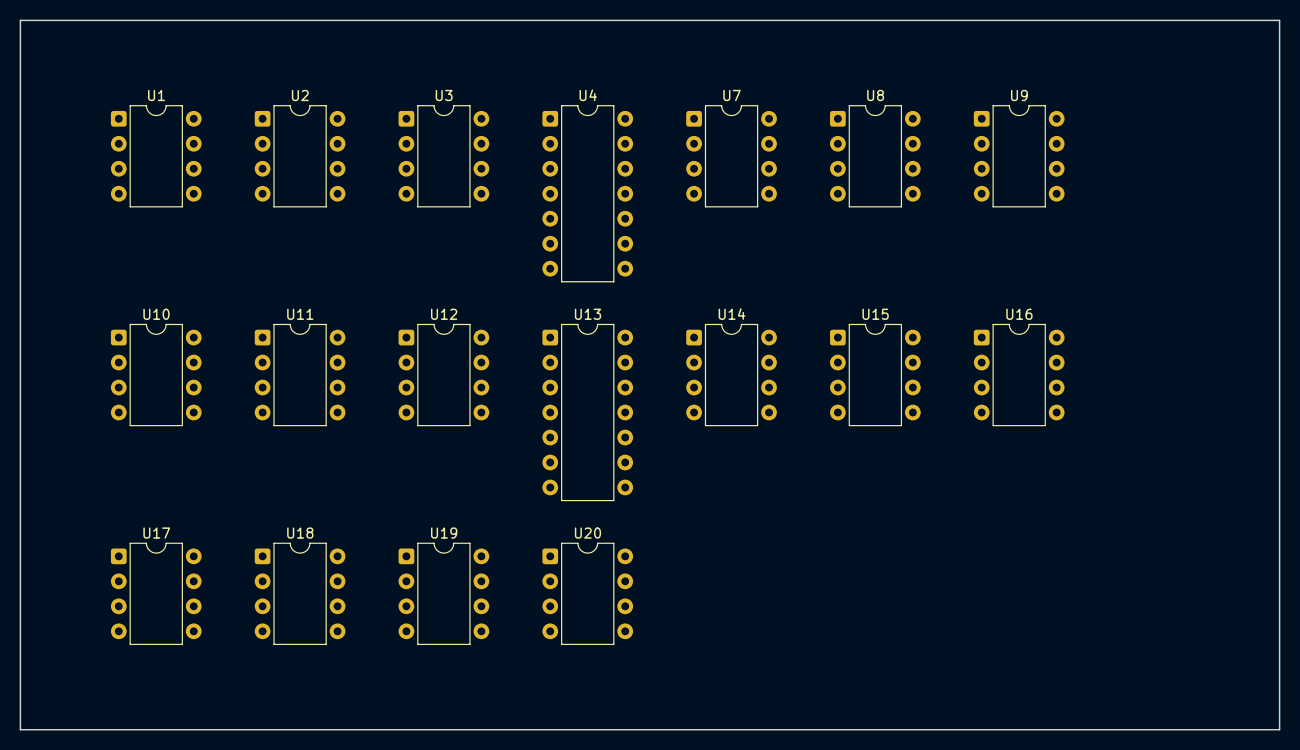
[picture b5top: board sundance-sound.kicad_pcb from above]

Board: 2 copper layers, 128.0 x 72.1 mm, 18 parts (0 on the bottom side), 11 nets, no tracks yet.

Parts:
U1, U2, U3, U8, U20: TL081; DIP-8_W7.62mm
U4: LM3900; DIP-14_W7.62mm
U7, U11, U14, U15, U16: LM555; DIP-8_W7.62mm
U9, U10, U12, U17, U18, U19: CA3080; DIP-8_W7.62mm
U13: 74LS125; DIP-14_W7.62mm

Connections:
+5V: U7.4, U7.8, U11.4, U11.8, U13.14, U14.4, U14.8, U15.4, U15.8, U16.4, U16.8
+15V: U2.7, U3.7, U4.14, U8.7, U9.7, U10.7, U12.7, U17.7, U18.7, U19.7, U20.7
-15V: U1.4, U2.4, U3.4, U8.4, U9.4, U10.4, U12.4, U17.4, U18.4, U19.4, U20.4
GND: U2.3, U3.3, U4.7, U7.1, U8.3, U11.1, U13.7, U14.1, U15.1, U16.1, U20.3
unnamed: U7.6, U7.7
unnamed: U11.6, U11.7
unnamed: U14.2, U14.6
unnamed: U15.2, U15.6
unnamed: U16.2, U16.6
unnamed: U13.2, U13.5, U13.9, U13.12
OUTPUT: U9.6, U10.6, U12.6, U17.6, U18.6, U19.6
